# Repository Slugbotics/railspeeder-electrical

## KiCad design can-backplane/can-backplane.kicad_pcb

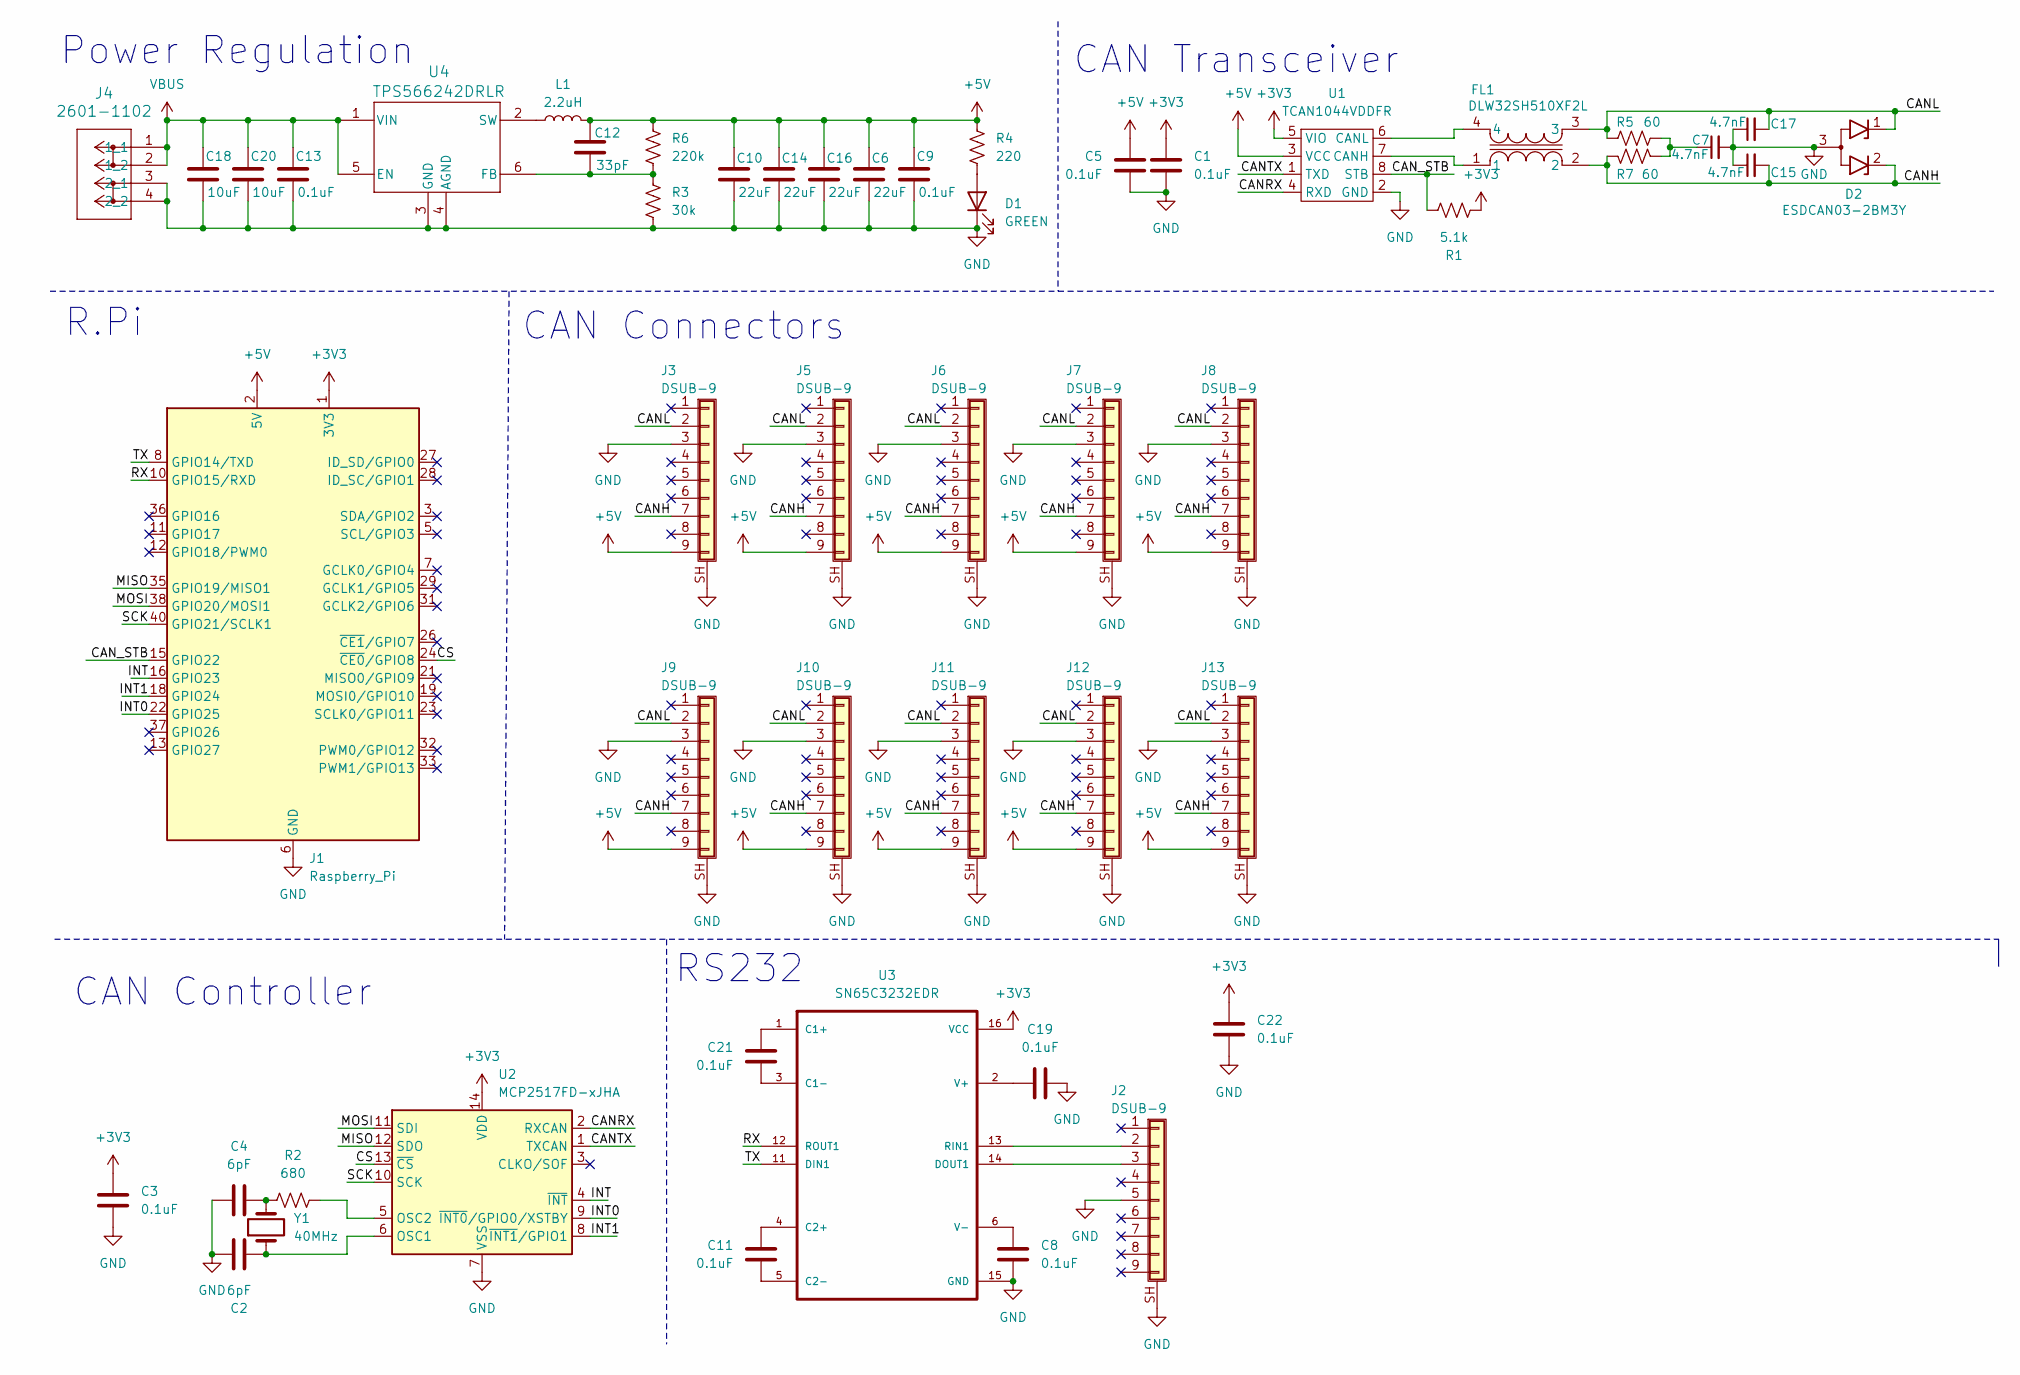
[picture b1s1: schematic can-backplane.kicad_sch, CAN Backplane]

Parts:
C1, C3, C5, C8, C9, C11, C13, C19, C21, C22: 0.1uF; C_0603_1608Metric
C2, C4: 6pF; C_0603_1608Metric
C6, C10, C14, C16: 22uF; C_0603_1608Metric
C7, C15, C17: 4.7nF; C_0603_1608Metric
C12: 33pF; C_0603_1608Metric
C18, C20: 10uF; C_0603_1608Metric
D1: GREEN; LED_0603_1608Metric
D2: ESDCAN03-2BM3Y; SOT-416
FL1: DLW32SH510XF2L; DLW32PH_MUR
J1: Raspberry_Pi; RPI_Hat_B+
J2, J3, J5, J6, J7, J8, J9, J10, J11, J12, J13: DSUB-9; DSUB-9_Female_Vertical_P2.77x2.84mm_MountingHoles
J4: 2601-1102; CONN2_2601-1102_WAG
L1: 2.2uH; L_Wurth_WE-LQSH-4020
R1: 5.1k; R_0603_1608Metric
R2: 680; R_0603_1608Metric
R3: 30k; R_0603_1608Metric
R4: 220; R_0603_1608Metric
R5, R7: 60; R_0603_1608Metric
R6: 220k; R_0603_1608Metric
U1: TCAN1044VDDFR; Texas_VSON-HR-8_1.5x2mm_P0.5mm
U2: MCP2517FD-xJHA; DFN-14-1EP_3x4.5mm_P0.65mm_EP1.65x4.25mm
U3: SN65C3232EDR; SOIC-16_3.9x9.9mm_P1.27mm
U4: TPS566242DRLR; SOT5x3_DRL_TEX
Y1: 40MHz; Crystal_SMD_Abracon_ABM10-4Pin_2.5x2.0mm

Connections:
+3V3: C1.1, C3.1, C22.1, J1.1 (3V3), J1.17 (3V3), R1.2, U1.5 (VIO), U2.14 (VDD), U3.16 (VCC)
+5V: C5.1, C6.1, C9.1, C10.1, C12.1, C14.1, C16.1, J1.2 (5V), J1.4 (5V), J3.9, J5.9, J6.9, J7.9, J8.9, J9.9, J10.9, J11.9, J12.9, J13.9, L1.2, R4.1, R6.1, U1.3 (VCC)
/CANH: C15.2, D2.2 (K2), FL1.2, J3.7, J5.7, J6.7, J7.7, J8.7, J9.7, J10.7, J11.7, J12.7, J13.7, R7.1
/CANL: C17.2, D2.1 (K1), FL1.3, J3.2, J5.2, J6.2, J7.2, J8.2, J9.2, J10.2, J11.2, J12.2, J13.2, R5.1
/CANRX: U1.4 (RXD), U2.2 (RXCAN)
/CANTX: U1.1 (TXD), U2.1 (TXCAN)
/CAN_STB: J1.15 (GPIO22), R1.1, U1.8 (STB)
/CS: J1.24 (~CE0/GPIO8), U2.13 (~CS)
/INT: J1.16 (GPIO23), U2.4 (~INT)
/INT0: J1.22 (GPIO25), U2.9 (~INT0/GPIO0/XSTBY)
/INT1: J1.18 (GPIO24), U2.8 (~INT1/GPIO1)
/MISO: J1.35 (GPIO19/MISO1), U2.12 (SDO)
/MOSI: J1.38 (GPIO20/MOSI1), U2.11 (SDI)
/RX: J1.10 (GPIO15/RXD), U3.12 (ROUT1)
/SCK: J1.40 (GPIO21/SCLK1), U2.10 (SCK)
/TX: J1.8 (GPIO14/TXD), U3.11 (DIN1)
GND: C1.2, C2.1, C3.2, C4.1, C5.2, C6.2, C7.2, C8.2, C9.2, C10.2, C13.2, C14.2, C15.1, C16.2, C17.1, C18.2, C19.2, C20.2, C22.2, D1.1 (K), D2.3 (A), J1.6 (GND), J1.9 (GND), J1.14 (GND), J1.20 (GND), J1.25 (GND), J1.30 (GND), J1.34 (GND), J1.39 (GND), J2.5, J2.SH (Shield), J3.3, J3.SH (Shield), J4.3 (2_1), J4.4 (2_2), J5.3, J5.SH (Shield), J6.3, J6.SH (Shield), J7.3, J7.SH (Shield), J8.3, J8.SH (Shield), J9.3, J9.SH (Shield), J10.3, J10.SH (Shield), J11.3, J11.SH (Shield), J12.3, J12.SH (Shield), J13.3, J13.SH (Shield), R3.2, U1.2 (GND), U2.7 (VSS), U2.15 (VSS), U3.15 (GND), U4.3 (GND), U4.4 (AGND)
unnamed: C4.2, R2.1, Y1.2
unnamed: C7.1, R5.2, R7.2
unnamed: D1.2 (A), R4.2
unnamed: J2.2, U3.13 (RIN1)
unnamed: J2.3, U3.14 (DOUT1)
unnamed: FL1.1, U1.7 (CANH)
unnamed: FL1.4, U1.6 (CANL)
unnamed: C2.2, U2.6 (OSC1), Y1.1
unnamed: R2.2, U2.5 (OSC2)
unnamed: C12.2, R3.1, R6.2, U4.6 (FB)
unnamed: L1.1, U4.2 (SW)
unnamed: C21.1, U3.1 (C1+)
unnamed: C21.2, U3.3 (C1-)
unnamed: C11.1, U3.4 (C2+)
unnamed: C11.2, U3.5 (C2-)
unnamed: C19.1, U3.2 (V+)
unnamed: C8.1, U3.6 (V-)
VBUS: C13.1, C18.1, C20.1, J4.1 (1_1), J4.2 (1_2), U4.1 (VIN), U4.5 (EN)

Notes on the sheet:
Power Regulation
R.Pi
CAN Controller
CAN Transceiver
RS232
CAN Connectors

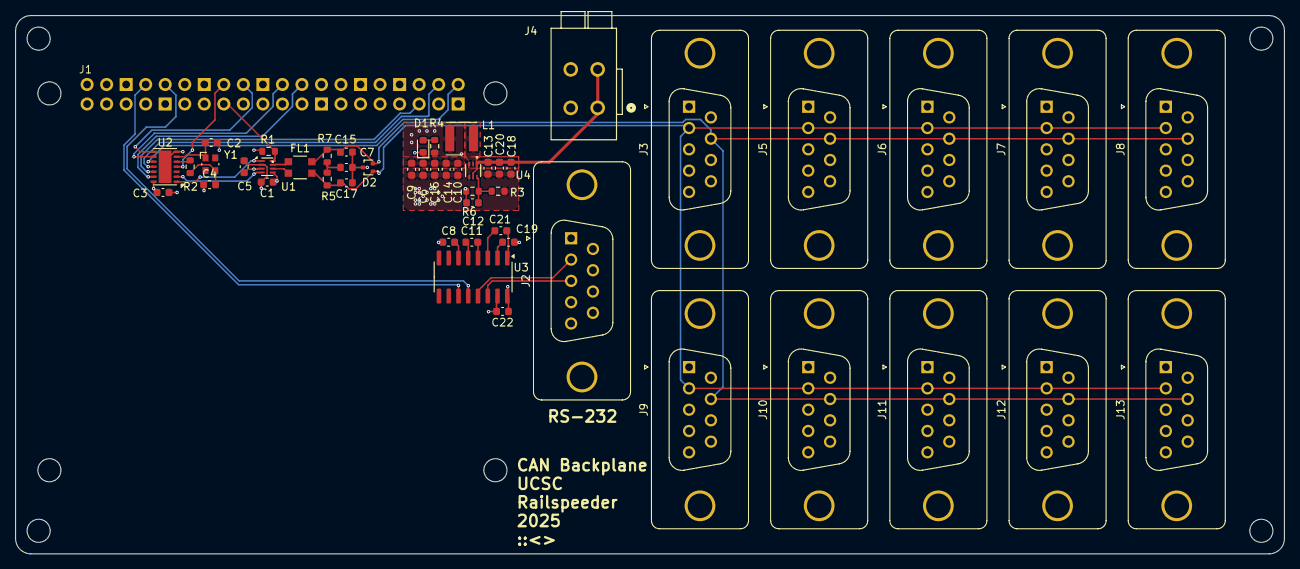
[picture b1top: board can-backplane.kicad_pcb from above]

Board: 4 copper layers, 165.0 x 70.0 mm, 51 parts (0 on the bottom side), 35 nets.

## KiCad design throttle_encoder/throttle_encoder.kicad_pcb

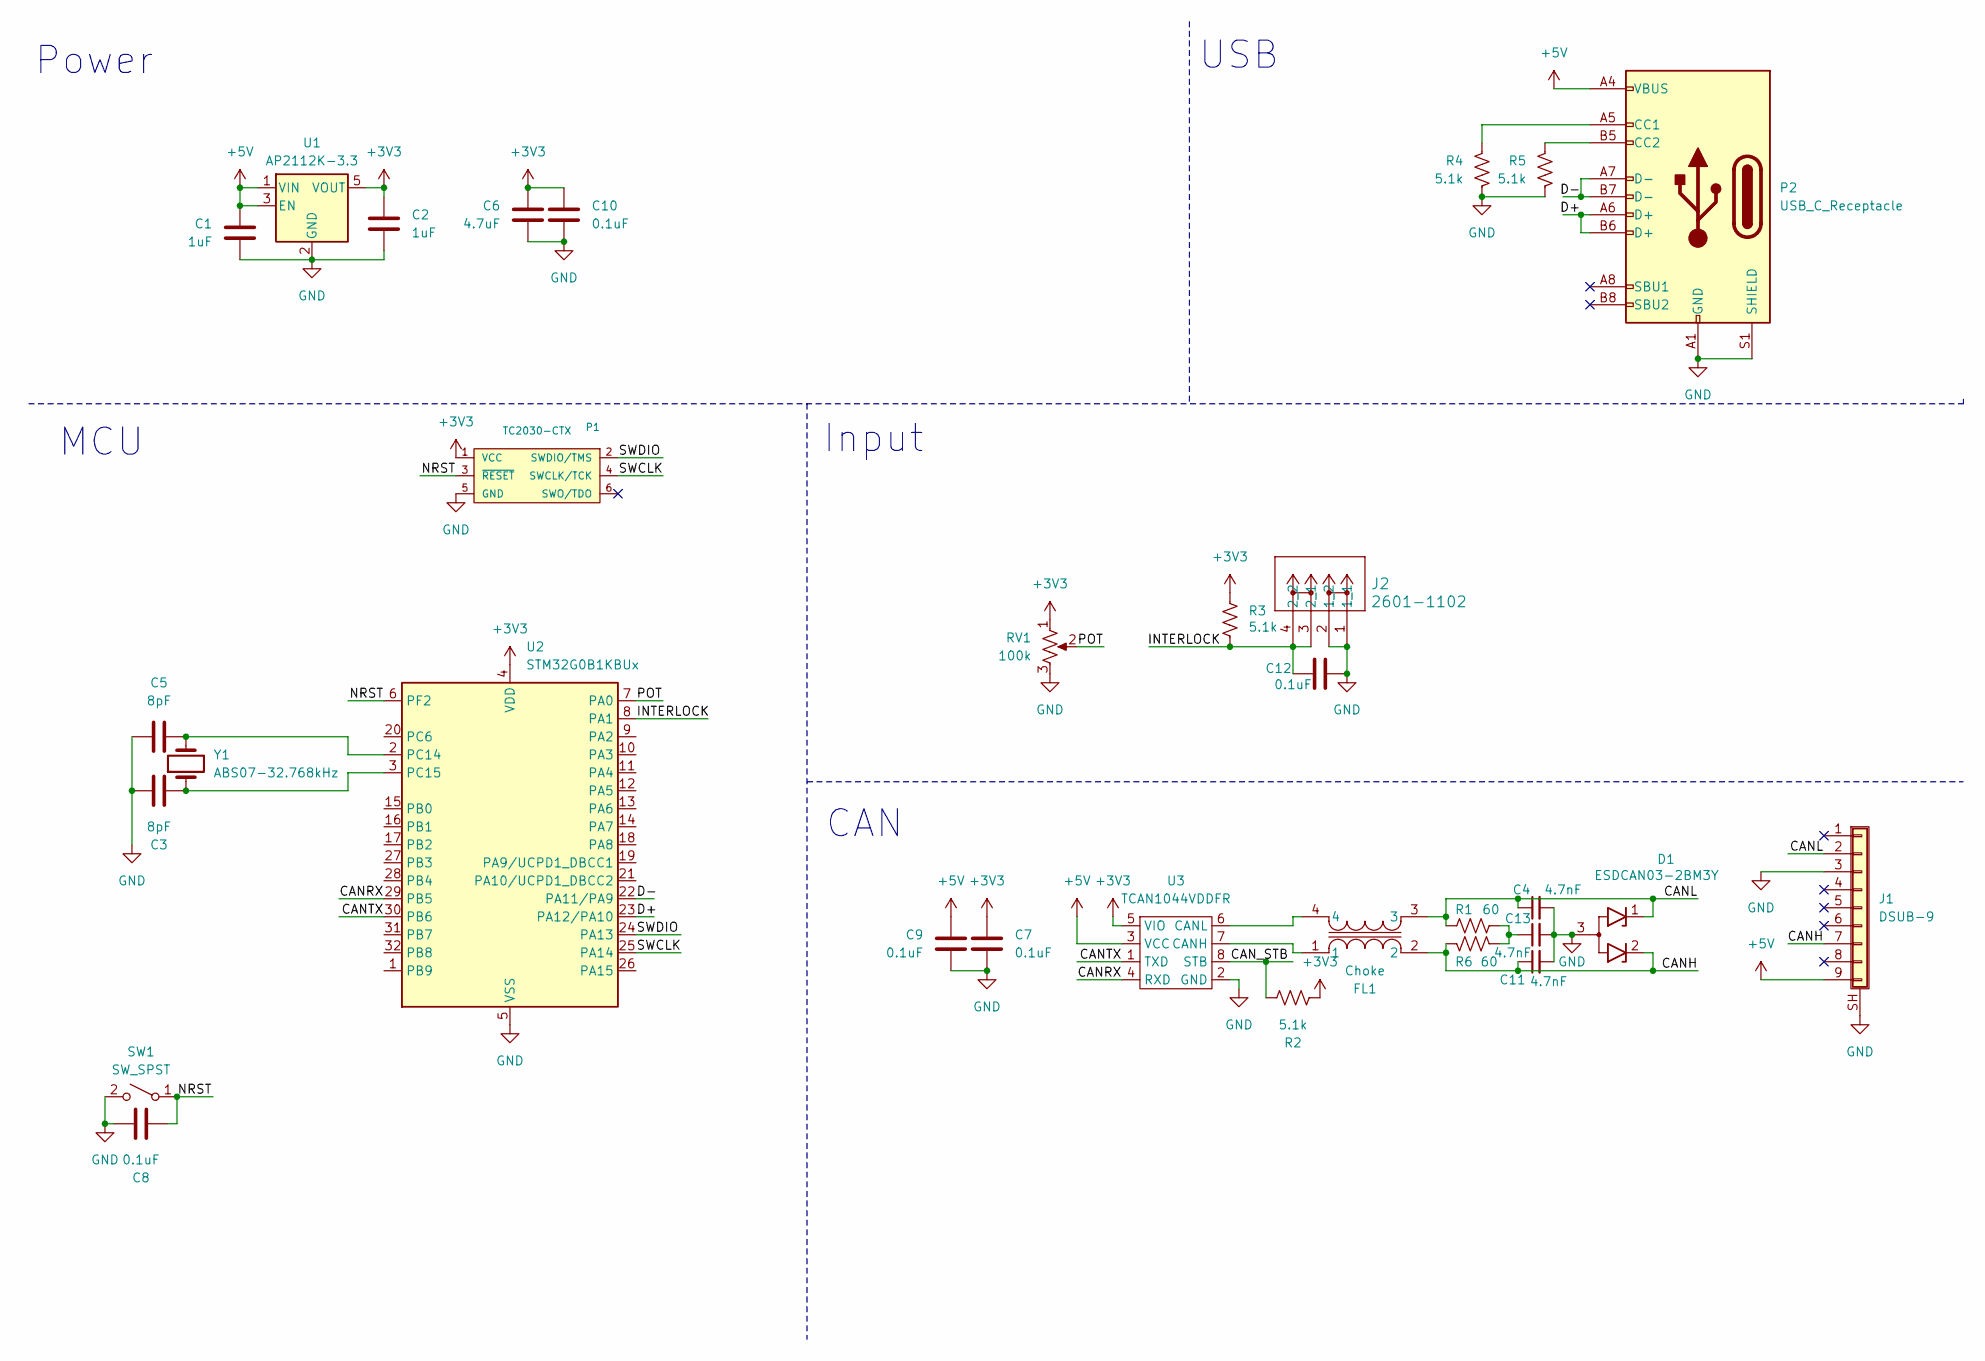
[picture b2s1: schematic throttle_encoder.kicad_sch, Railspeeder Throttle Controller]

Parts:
C1, C2: 1uF; C_0402_1005Metric
C3, C5: 8pF; C_0402_1005Metric
C4, C11, C13: 4.7nF; C_0402_1005Metric
C6: 4.7uF; C_0402_1005Metric
C7, C8, C9, C10, C12: 0.1uF; C_0402_1005Metric
D1: ESDCAN03-2BM3Y; SOT-416
FL1: Choke; DLW32PH_MUR
J1: DSUB-9; DSUB-9_Female_Vertical_P2.77x2.84mm_MountingHoles
J2: 2601-1102; CONN2_2601-1102_WAG
P1: TC2030-CTX; Tag-Connect_TC2030-IDC-FP_2x03_P1.27mm_Vertical
P2: USB_C_Receptacle; USB_C_Receptacle_HCTL_HC-TYPE-C-16P-01A
R1, R6: 60; R_0402_1005Metric
R2, R3, R4, R5: 5.1k; R_0402_1005Metric
RV1: 100k; Potentiometer_Bourns_PTV09A-1_Single_Vertical
SW1: SW_SPST; SW_SPST_B3U-1000P
U1: AP2112K-3.3; SOT-23-5
U2: STM32G0B1KBUx; QFN-32-1EP_5x5mm_P0.5mm_EP3.45x3.45mm
U3: TCAN1044VDDFR; Texas_S-PVSON-N8
Y1: ABS07-32.768kHz; Crystal_SMD_MicroCrystal_CC7V-T1A-2Pin_3.2x1.5mm

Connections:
+3V3: C2.1, C6.1, C7.1, C10.1, P1.1 (VCC), R2.2, R3.1, RV1.1, U1.5 (VOUT), U2.4 (VDD), U3.5 (VIO)
+5V: C1.1, C9.1, J1.9, P2.A4 (VBUS), P2.A9 (VBUS), P2.B4 (VBUS), P2.B9 (VBUS), U1.1 (VIN), U1.3 (EN), U3.3 (VCC)
/CANH: C11.1, D1.2 (K2), FL1.2, J1.7, R6.1
/CANL: C4.1, D1.1 (K1), FL1.3, J1.2, R1.1
/CANRX: U2.29 (PB5), U3.4 (RXD)
/CANTX: U2.30 (PB6), U3.1 (TXD)
/CAN_STB: R2.1, U3.8 (STB)
/D+: P2.A6 (D+), P2.B6 (D+), U2.23 (PA12/PA10)
/D-: P2.A7 (D-), P2.B7 (D-), U2.22 (PA11/PA9)
/INTERLOCK: C12.1, J2.3 (2_1), J2.4 (2_2), R3.2, U2.8 (PA1)
/NRST: C8.2, P1.3 (~RESET), SW1.1 (A), U2.6 (PF2)
/POT: RV1.2, U2.7 (PA0)
/SWCLK: P1.4 (SWCLK/TCK), U2.25 (PA14)
/SWDIO: P1.2 (SWDIO/TMS), U2.24 (PA13)
GND: C1.2, C2.2, C3.1, C4.2, C5.2, C6.2, C7.2, C8.1, C9.2, C10.2, C11.2, C12.2, C13.2, D1.3 (A), J1.3, J1.SH (Shield), J2.1 (1_1), J2.2 (1_2), P1.5 (GND), P2.A1 (GND), P2.A12 (GND), P2.B1 (GND), P2.B12 (GND), P2.S1 (SHIELD), R4.2, R5.2, RV1.3, SW1.2 (B), U1.2 (GND), U2.5 (VSS), U2.33 (VSS), U3.2 (GND)
unnamed: C13.1, R1.2, R6.2
unnamed: P2.A5 (CC1), R4.1
unnamed: P2.B5 (CC2), R5.1
unnamed: C5.1, U2.2 (PC14), Y1.2
unnamed: C3.2, U2.3 (PC15), Y1.1
unnamed: FL1.1, U3.7 (CANH)
unnamed: FL1.4, U3.6 (CANL)

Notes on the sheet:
USB
MCU
Input
Power
CAN

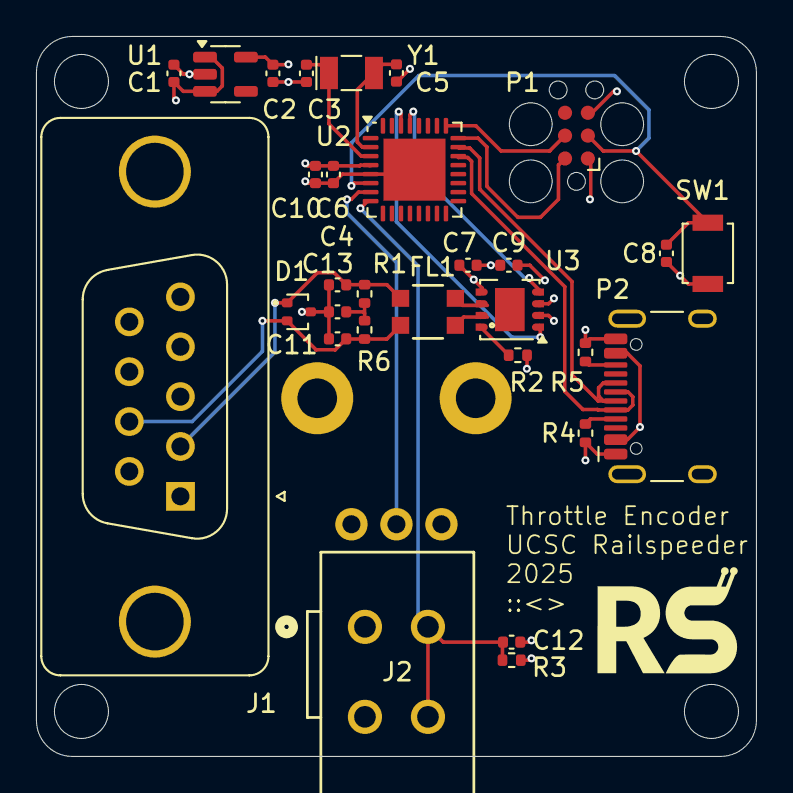
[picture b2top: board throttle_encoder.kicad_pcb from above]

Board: 4 copper layers, 40.0 x 40.0 mm, 31 parts (1 on the bottom side), 22 nets.

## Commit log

2025-03-05 Project creation
2025-03-05 Schematic work
2025-03-05 rename
2025-03-05 Backplane schem work
2025-03-05 Added serial
2025-03-05 Adjusted lib path
2025-03-05 Added level shifting
2025-03-05 Formatting
2025-03-06 Component selection
2025-03-06 PCB Work
2025-03-06 Added board graphics
2025-03-06 Component grouping
2025-03-07 Project commit
2025-03-07 Fabrication
2025-03-07 Silkscreen
2025-03-07 Cut in half
2025-03-07 PCB work for final fab
2025-03-07 Finishing touches
2025-03-08 Sweeping via resizing
2025-03-09 Patched missing trace
